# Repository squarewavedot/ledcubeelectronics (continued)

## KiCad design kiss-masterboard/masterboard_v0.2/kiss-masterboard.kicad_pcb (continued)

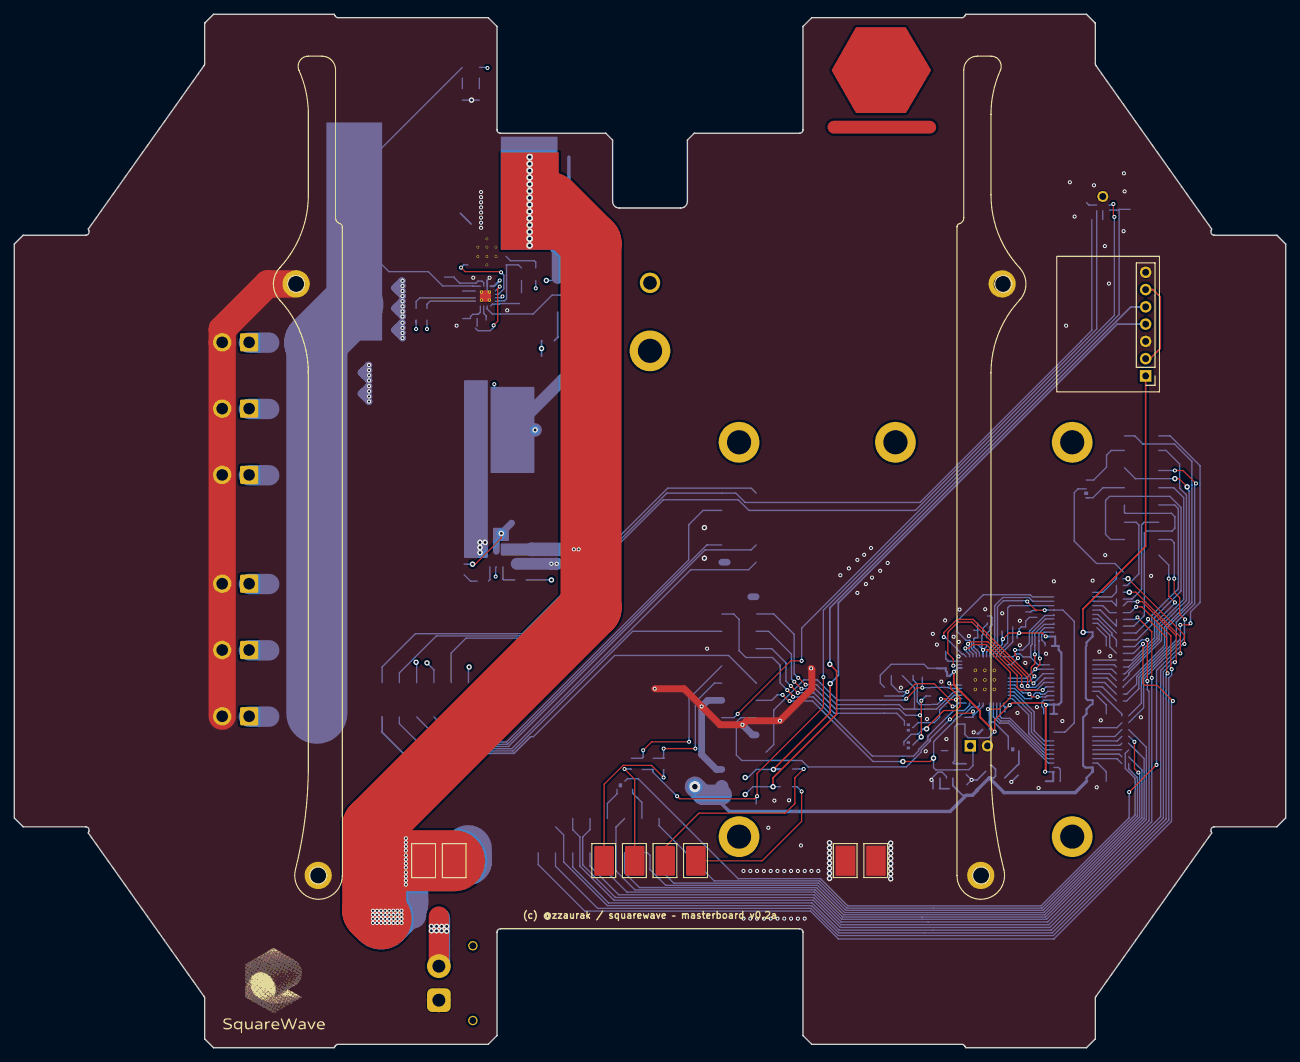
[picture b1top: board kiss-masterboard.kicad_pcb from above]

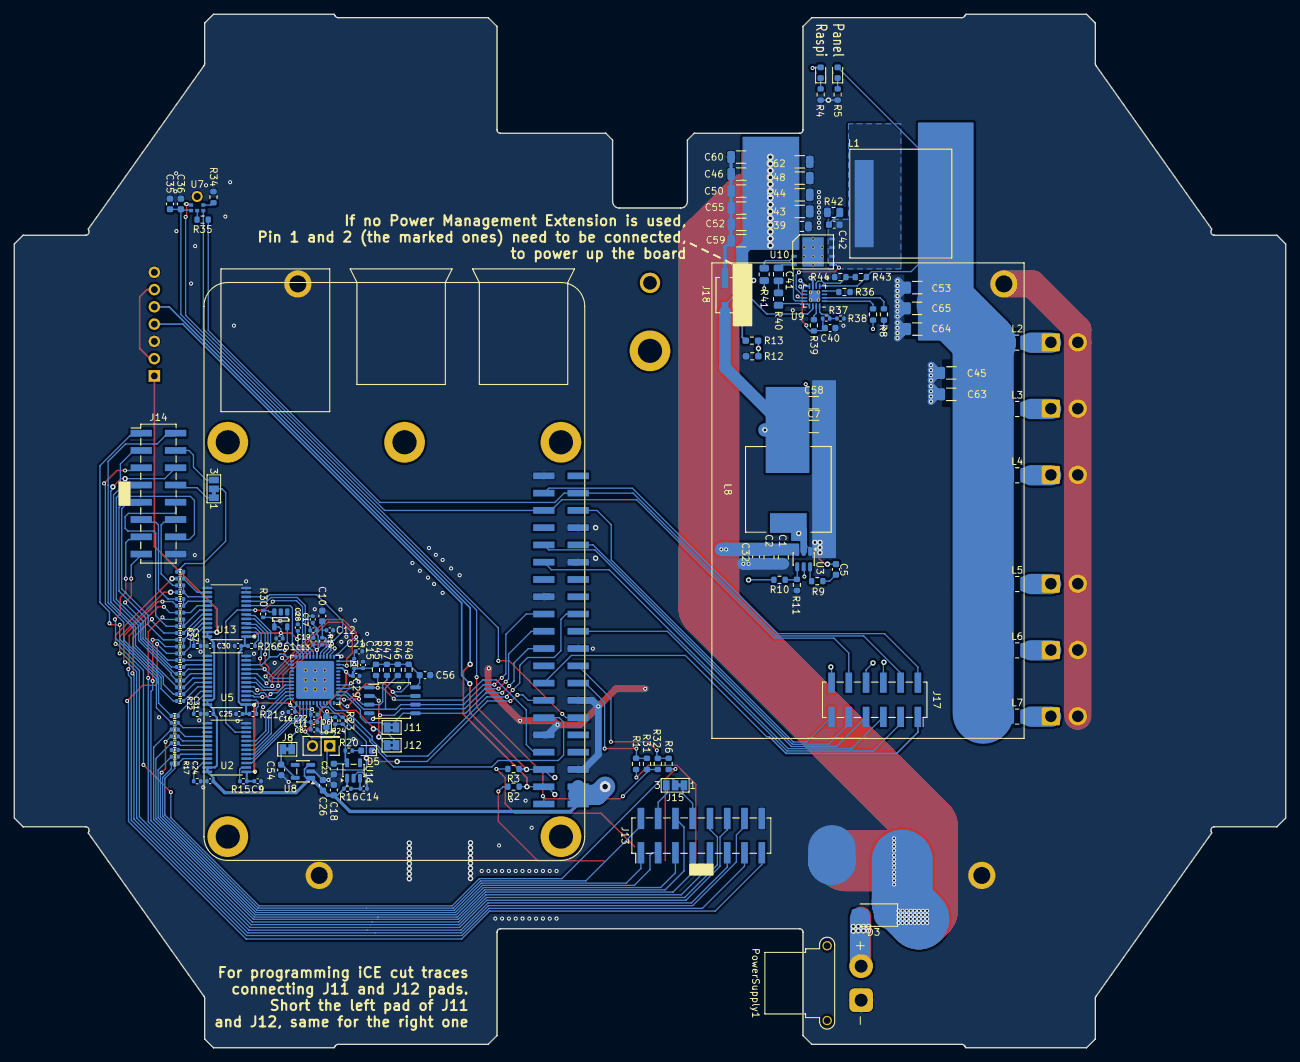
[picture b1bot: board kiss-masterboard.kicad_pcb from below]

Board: 4 copper layers, 187.0 x 152.0 mm, 172 parts (162 on the bottom side), 157 nets.

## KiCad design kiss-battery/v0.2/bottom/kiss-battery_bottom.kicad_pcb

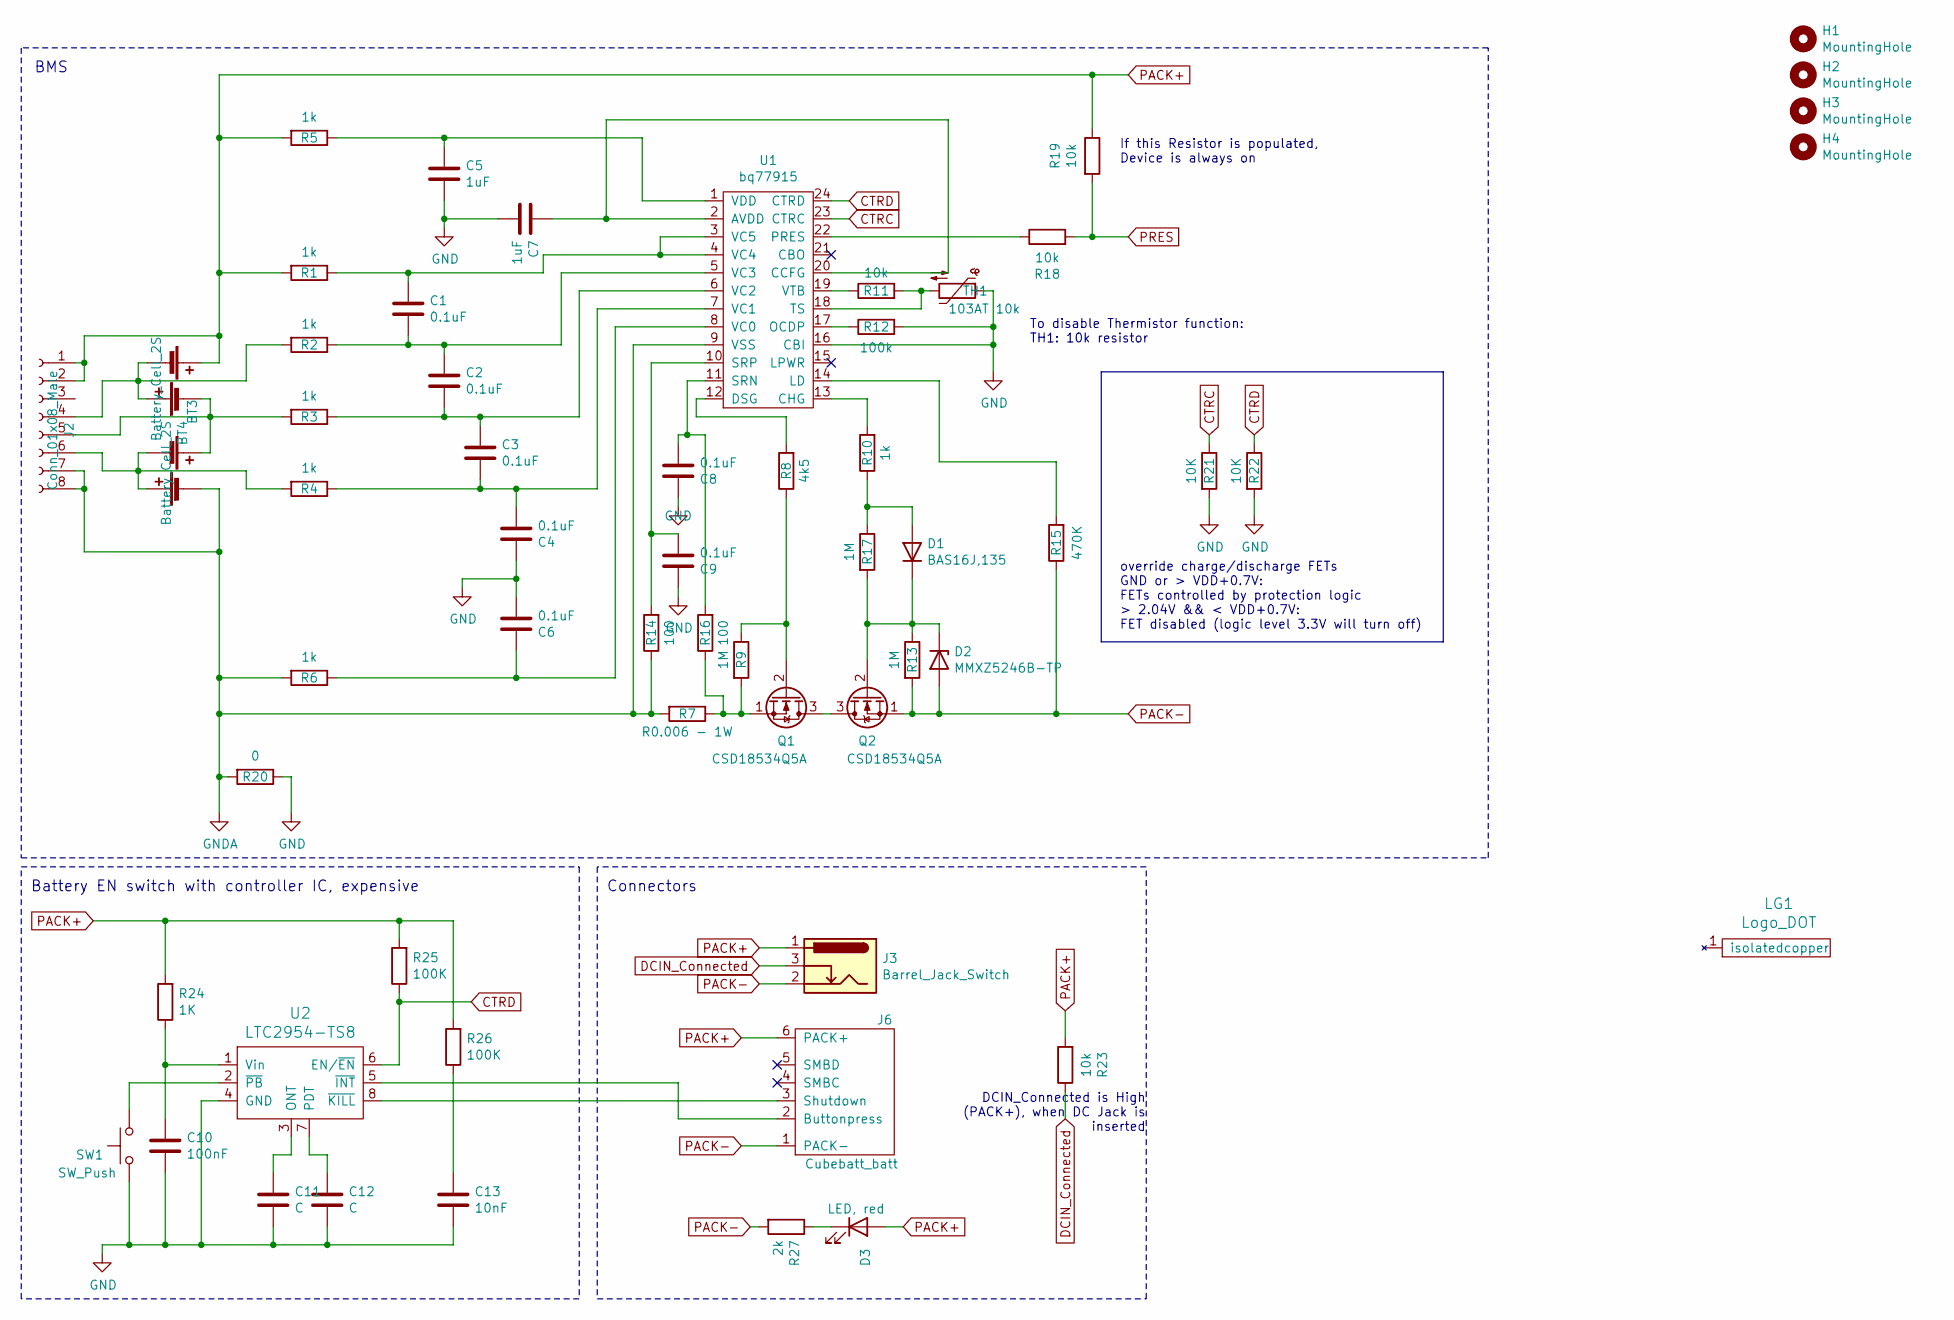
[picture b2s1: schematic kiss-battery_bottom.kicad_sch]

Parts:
BT3, BT4: Battery_Cell_2S; Battholder_18650x2_BLM
C1, C2, C3, C4, C6, C8, C9: 0.1uF; C_0603_1608Metric
C5, C7: 1uF; C_0603_1608Metric
C10: 100nF; C_0603_1608Metric
C11, C12: C; C_0603_1608Metric
C13: 10nF; C_0603_1608Metric
D1: BAS16J,135; D_SOD-323F
D2: MMXZ5246B-TP; D_SOD-323
D3: LED, red; LED_0603_1608Metric; Part No. LB Q39G-L2N2-35-1
H1, H2, H3, H4: MountingHole; MountingHole_3.2mm_M3_ISO14580
J2: Conn_01x08_Male; PinSocket_1x08_P2.54mm_Vertical_SMD_Pin1Left
J3: Barrel_Jack_Switch; DC_Jack_PJ-036BH-SMT
J6: Cubebatt_batt; cube_battery_connector_battside
LG1: Logo_DOT; Logo_Squarewave_Text_15mm_Silks
Q1, Q2: CSD18534Q5A; VSONP-8-1EP_5x6_P1.27mm
R1, R2, R3, R4, R5, R6, R10: 1k; R_0805_2012Metric
R7: R0.006 - 1W; R_2010_5025Metric
R8: 4k5; R_0603_1608Metric
R9, R13, R17: 1M; R_0603_1608Metric
R11, R18, R19, R23: 10k; R_0603_1608Metric
R12: 100k; R_0603_1608Metric
R14, R16: 100; R_0603_1608Metric
R15: 470K; R_0603_1608Metric
R20: 0; R_0805_2012Metric
R21, R22: 10K; R_0603_1608Metric
R24: 1K; R_0603_1608Metric
R25, R26: 100K; R_0603_1608Metric
R27: 2k; R_0603_1608Metric_Pad1.05x0.95mm_HandSolder; Part No. RC0603JR-07680R
SW1: SW_Push; Tact_Switch_Side_Boss_B3U-3000P-B
TH1: 103AT 10k; R_0603_1608Metric
U1: bq77915; TSSOP-24_4.4x7.8mm_P0.65mm
U2: LTC2954-TS8; TSOT-23-8

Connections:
CTRC: R21.1, U1.23 (CTRC)
CTRD: R22.1, R25.1, U1.24 (CTRD), U2.6 (EN/~EN)
DCIN_Connected: J3.3, R23.1
GND: C4.1, C5.2, C6.2, C7.2, C8.1, C9.1, C10.1, C11.2, C12.2, C13.2, R12.2, R20.1, R21.2, R22.2, SW1.2, TH1.1, U1.16 (CBI), U2.4 (GND)
GNDA: BT3.4 (2N), J2.7, J2.8, R6.2, R7.2, R14.1, R20.2, U1.9 (VSS)
unnamed: BT3.1 (1P), BT4.4 (2N), J2.5, R3.2
unnamed: BT3.2 (1N), BT3.3 (2P), J2.6, R4.2
unnamed: BT4.2 (1N), BT4.3 (2P), J2.4, R2.2
unnamed: C1.1, R1.1, U1.3 (VC5), U1.4 (VC4)
unnamed: C1.2, C2.1, R2.1, U1.5 (VC3)
unnamed: C2.2, C3.1, R3.1, U1.6 (VC2)
unnamed: C3.2, C4.2, R4.1, U1.7 (VC1)
unnamed: C5.1, R5.1, U1.1 (VDD)
unnamed: C6.1, R6.1, U1.8 (VC0)
unnamed: C7.1, U1.2 (AVDD), U1.20 (CCFG)
unnamed: C8.2, R16.2, U1.11 (SRN)
unnamed: C9.2, R14.2, U1.10 (SRP)
unnamed: C10.2, R24.1, U2.1 (Vin)
unnamed: C11.1, U2.3 (ONT)
unnamed: C12.1, U2.7 (PDT)
unnamed: C13.1, R26.1
unnamed: D1.1 (K), D2.1 (K), Q2.2 (G), R13.1, R17.2
unnamed: D1.2 (A), R10.1, R17.1
unnamed: D3.1 (K), R27.1
unnamed: J6.2 (Buttonpress), U2.5 (~INT)
unnamed: J6.3 (Shutdown), U2.8 (~KILL)
unnamed: Q1.1 (S), R7.1, R9.2, R16.1
unnamed: Q1.2 (G), R8.1, R9.1
unnamed: Q1.3 (D), Q2.3 (D)
unnamed: R8.2, U1.12 (DSG)
unnamed: R10.2, U1.13 (CHG)
unnamed: R11.1, U1.19 (VTB)
unnamed: R11.2, TH1.2, U1.18 (TS)
unnamed: R12.1, U1.17 (OCDP)
unnamed: R15.2, U1.14 (LD)
unnamed: R18.1, U1.22 (PRES)
unnamed: SW1.1, U2.2 (~PB)
PACK+: BT4.1 (1P), D3.2 (A), J2.1, J2.2, J3.1, J6.6 (PACK+), R1.2, R5.2, R19.1, R23.2, R24.2, R25.2, R26.2
PACK-: D2.2 (A), J3.2, J6.1 (PACK-), Q2.1 (S), R13.2, R15.1, R27.2
PRES: R18.2, R19.2

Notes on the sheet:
Connectors
If this Resistor is populated, Device is always on
override charge/discharge FETs GND or > VDD+0.7V: FETs controlled by protection logic > 2.04V && < VDD+0.7V: FET disabled (logic level 3.3V will turn off)
DCIN_Connected is High (PACK+), when DC Jack is inserted
BMS
Battery EN switch with controller IC, expensive
To disable Thermistor function: TH1: 10k resistor

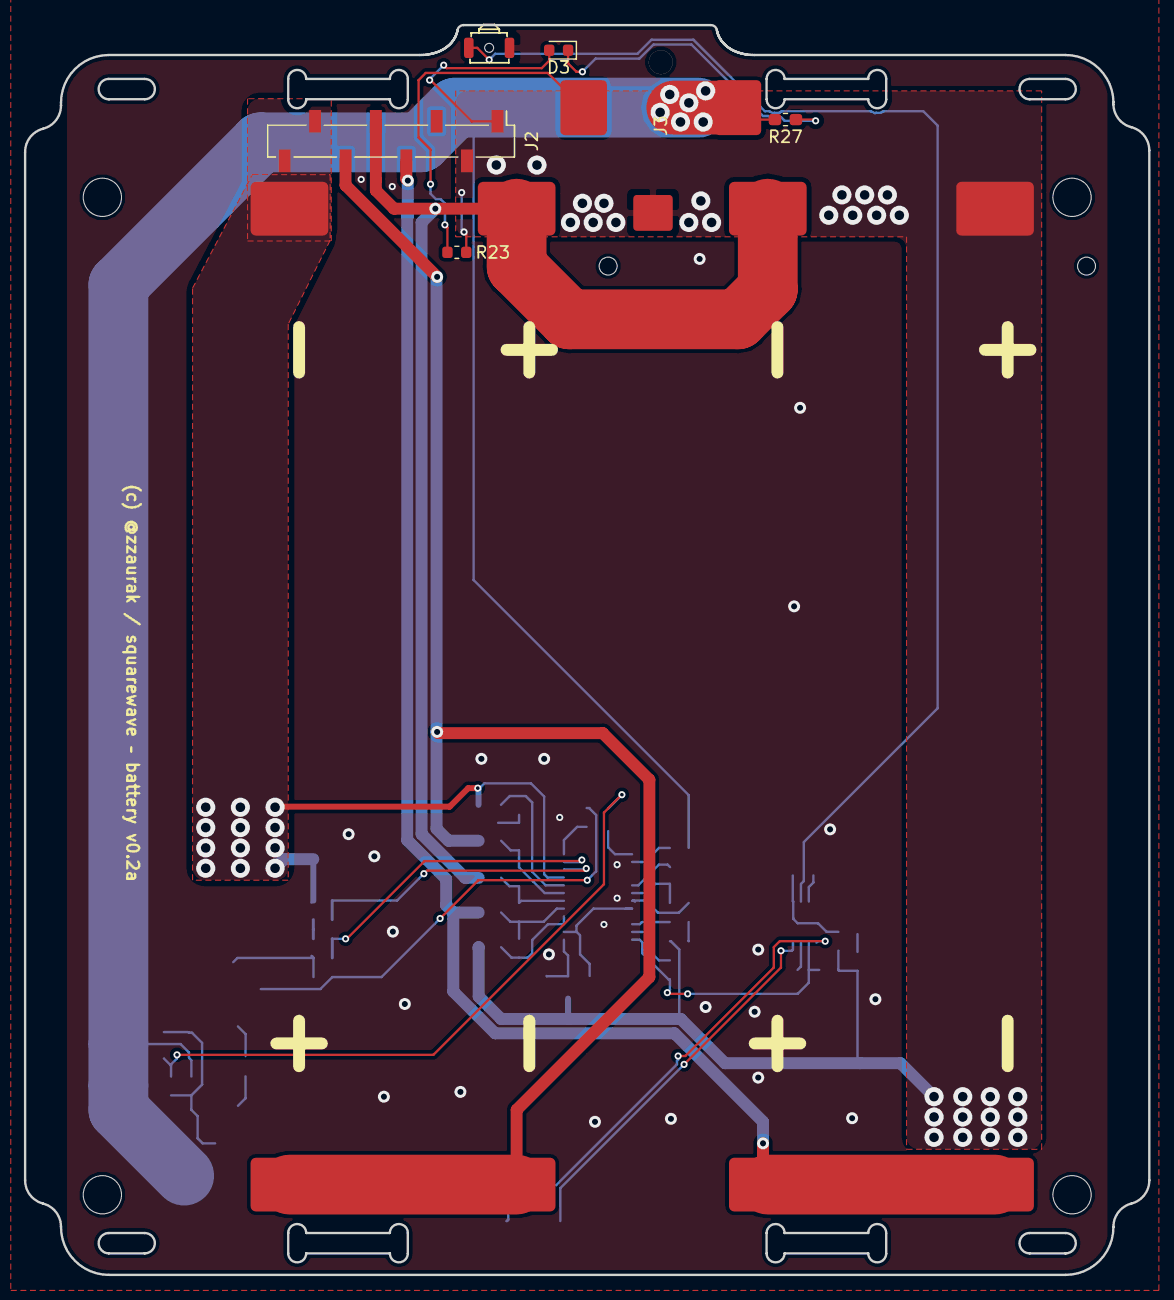
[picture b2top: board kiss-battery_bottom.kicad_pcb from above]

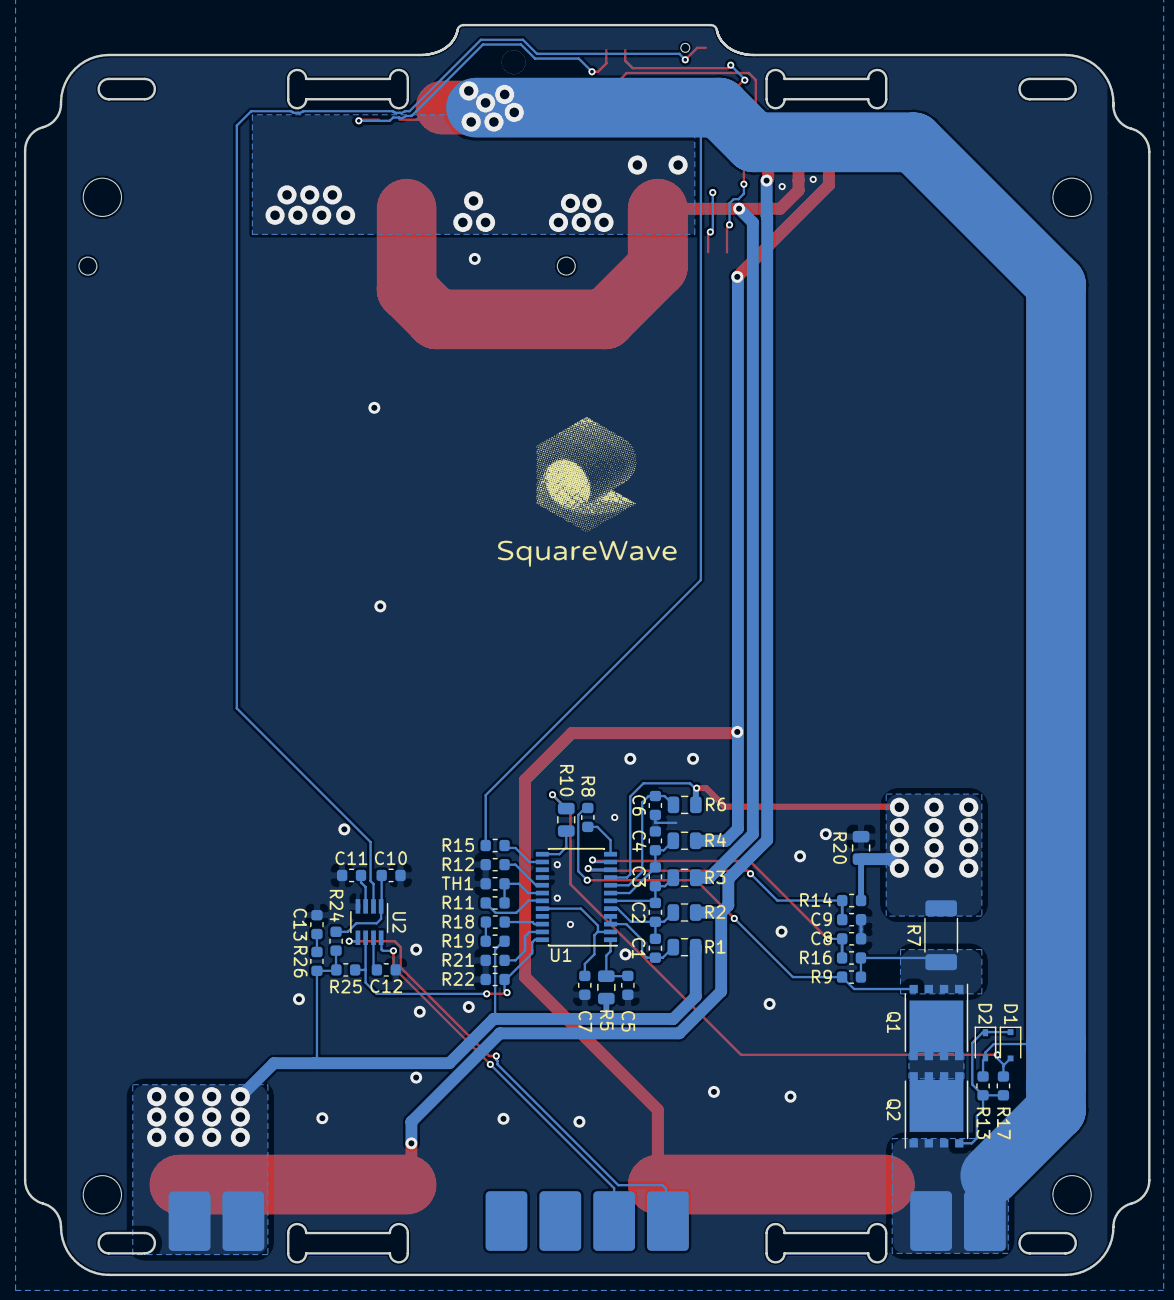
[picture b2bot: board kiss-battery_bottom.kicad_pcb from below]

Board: 2 copper layers, 94.0 x 104.5 mm, 59 parts (46 on the bottom side), 40 nets.

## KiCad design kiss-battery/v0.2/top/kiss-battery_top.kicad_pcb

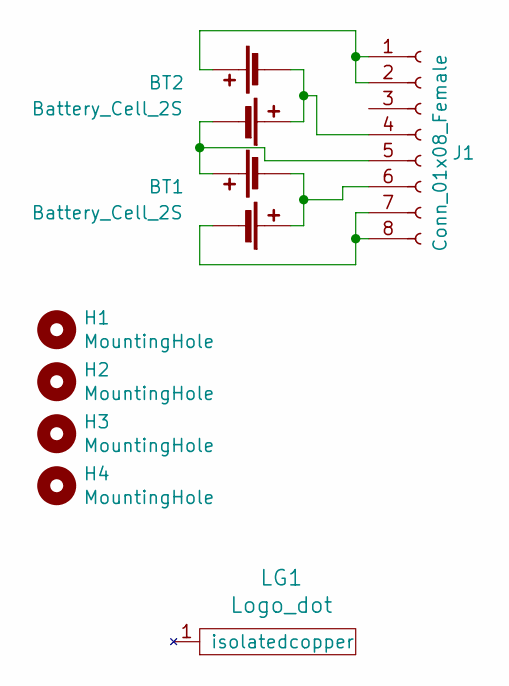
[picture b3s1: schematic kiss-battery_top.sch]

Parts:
BT1, BT2: Battery_Cell_2S; Battholder_18650x2_BLM
H1, H2, H3, H4: MountingHole; MountingHole_3.2mm_M3_ISO14580
J1: Conn_01x08_Female; PinSocket_1x08_P2.54mm_Vertical_SMD_Pin1Left
LG1: Logo_dot; Logo_Dot_15mm_Text_Mask

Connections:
unnamed: BT1.1 (1P), BT1.4 (2N), J1.6
unnamed: BT1.2 (1N), J1.7, J1.8
unnamed: BT1.3 (2P), BT2.2 (1N), J1.5
unnamed: BT2.1 (1P), BT2.4 (2N), J1.4
unnamed: BT2.3 (2P), J1.1, J1.2

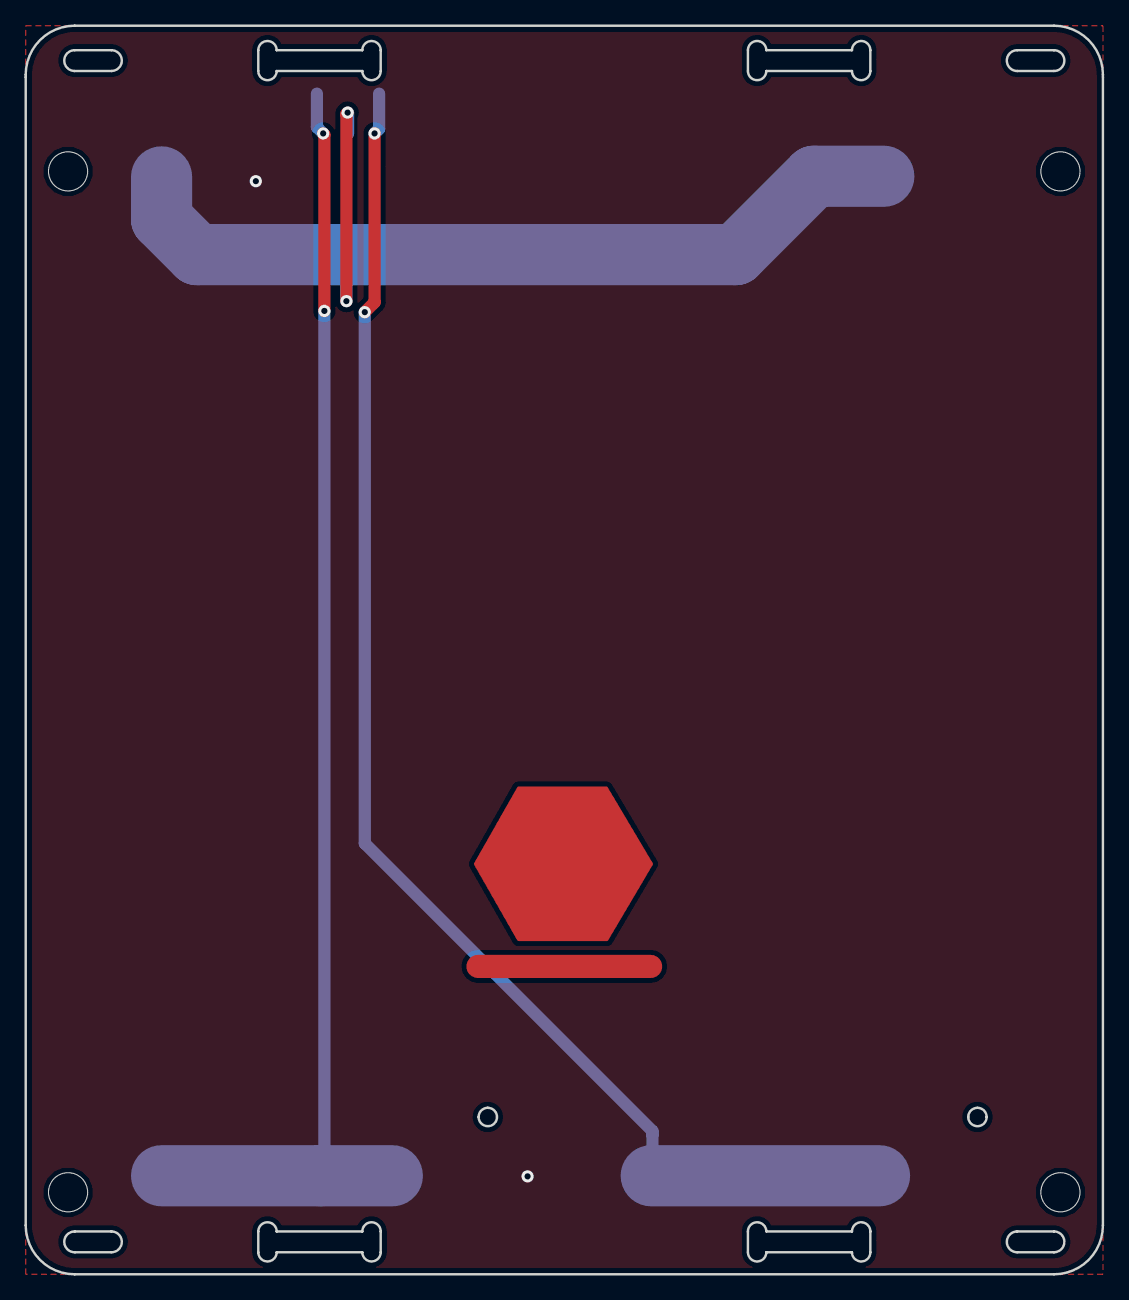
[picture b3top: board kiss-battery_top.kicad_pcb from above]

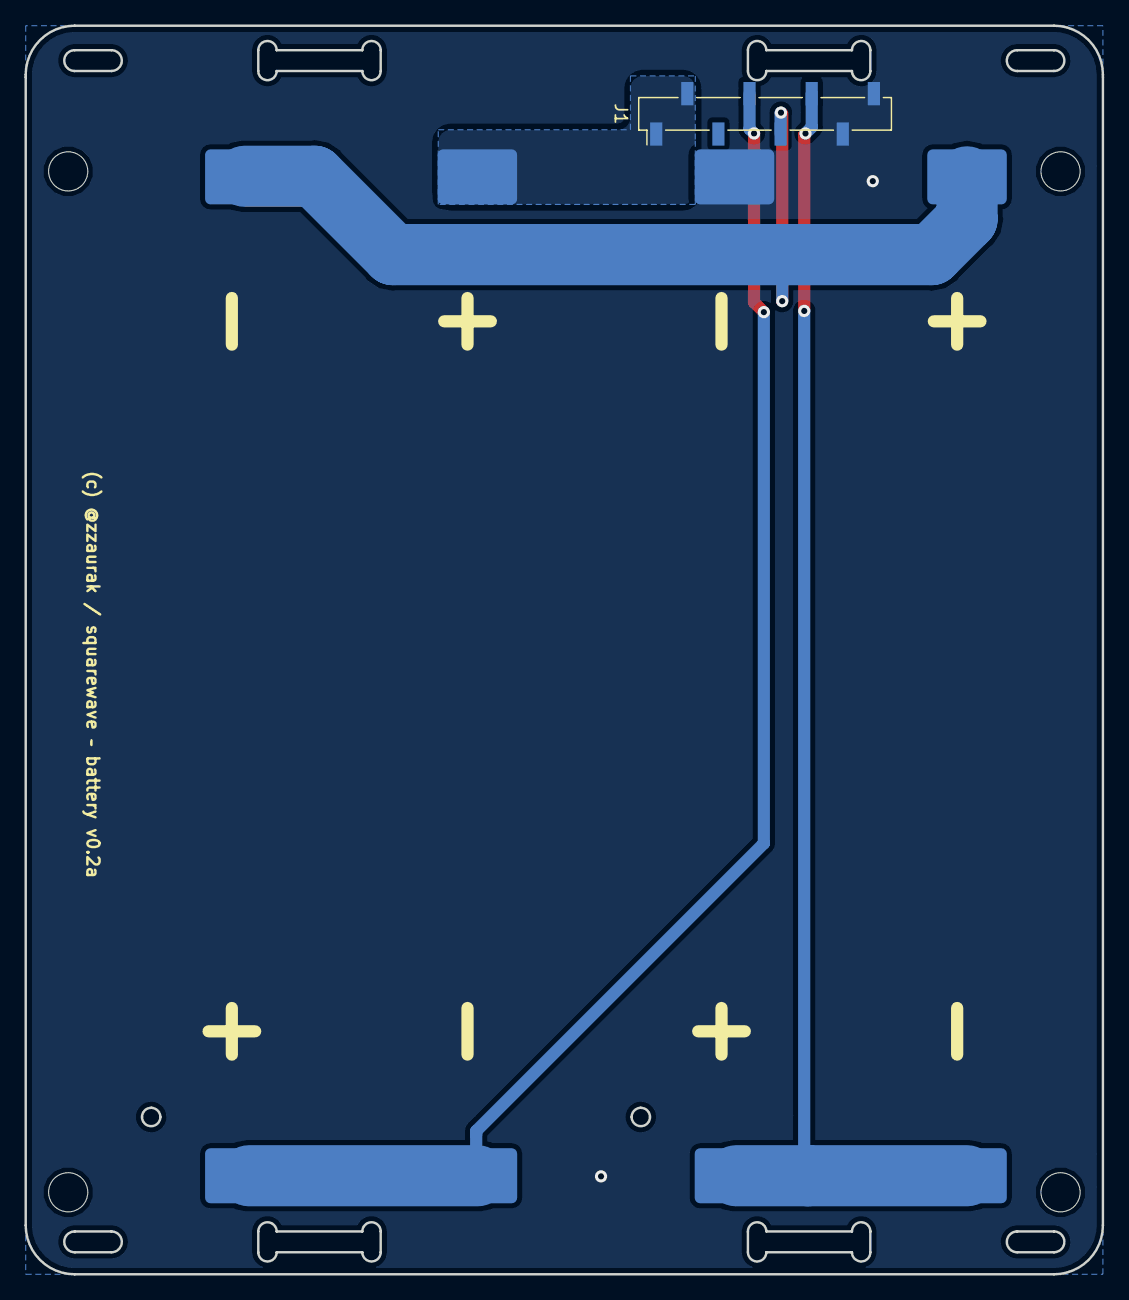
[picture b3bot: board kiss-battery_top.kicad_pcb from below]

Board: 2 copper layers, 88.0 x 102.0 mm, 8 parts (3 on the bottom side), 5 nets.

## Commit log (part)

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2026-04-28 add missing symbols
2026-04-28 wip: Added missing symbols, adjusted pcb layout
2026-05-04 add kiss-battery v0.2 bottom schematic, image exports, and BMS datasheets
2026-05-05 replaced resistor array with normal resistors
2026-05-05 replaced symbosl with standart symbols and reduced DRC errorsMAX98357A and TLV75709PDBV symbols
2026-05-12 Fix DRC issues
2026-05-19 Adjust to new batterypack,
2026-06-08 Replaced TPS54327 with TPS56339DDC and adjusted the schematic layout accordingly.
2026-06-09 Add extension header
2026-06-23 Added IMU, routed extension layer, switched battery polarity
2026-06-30 add cnumbers initial order v04a
